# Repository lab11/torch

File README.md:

Torch
=====

<center>

</center>

This system provides the hardware and software for a software-defined lighting platform.

Compile
-------

    git clone https://github.com/lab11/contiki
    cd contiki
    git co sdl

    cd ../torch/contiki/apps/coap
    make

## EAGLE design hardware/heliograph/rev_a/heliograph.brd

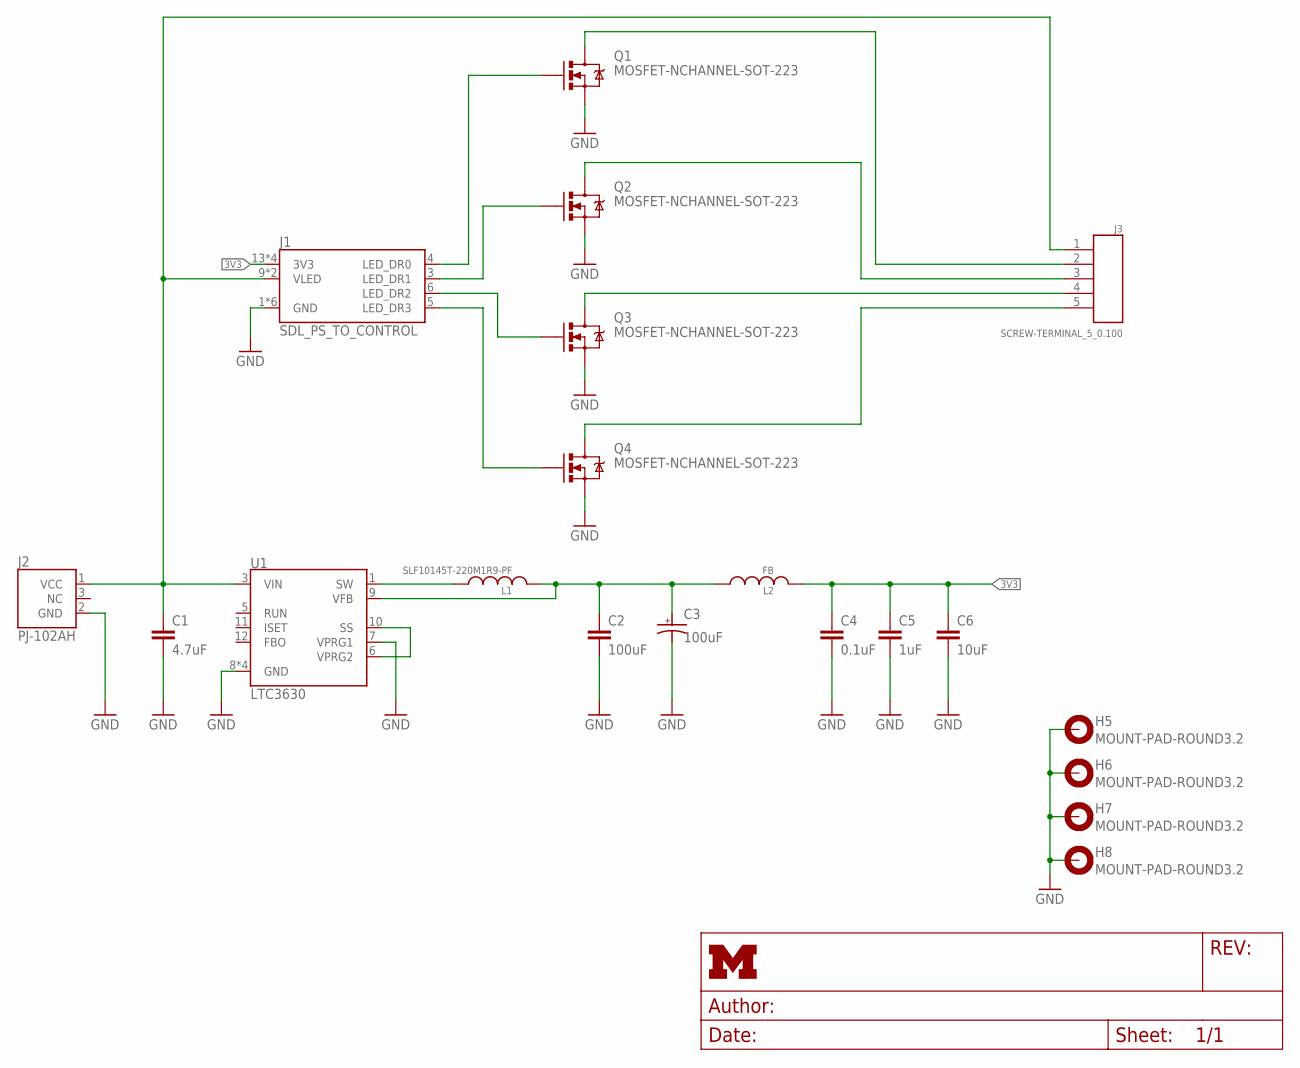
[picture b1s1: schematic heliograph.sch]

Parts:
C1: 4.7uF; C2220K; DIGIKEY 445-1450-1-ND
C2: 100uF; C1210; DIGIKEY 1276-3364-1-ND
C3: 100uF; 2917-POL; DIGIKEY 399-3769-1-ND
C4: 0.1uF; C0603; DIGIKEY 445-1316-1-ND
C5: 1uF; C0603; DIGIKEY 445-1604-1-ND
C6: 10uF; C0603; DIGIKEY 445-9065-1-ND
H5, H6, H7, H8: MOUNT-PAD-ROUND3.2; 3,2-PAD
J1: SDL_PS_TO_CONTROL
J2: PJ-102AH
J3: SCREW-TERMINAL_5_0.100; CONN_BLOCK_5
L1: SLF10145T-220M1R9-PF; SLF10145
L2: FB; 0603_CAP; DIGIKEY 490-1011-1-ND
Q1, Q2, Q3, Q4: MOSFET-NCHANNEL-SOT-223; SOT-223; DIGIKEY 568-9714-1-ND
U1: LTC3630; MSOP-16(12)

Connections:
3V3: C4.1, C5.1, C6.1, J1.13 (3V3), J1.14 (3V3), J1.15 (3V3), J1.16 (3V3), L2.2
GND: C1.2, C2.2, C3.- (ANODE), C4.2, C5.2, C6.2, H5.B3,2, H6.B3,2, H7.B3,2, H8.B3,2, J1.1 (GND), J1.2 (GND), J1.7 (GND), J1.8 (GND), J1.11 (GND), J1.12 (GND), J2.2 (GND), Q1.3 (S), Q2.3 (S), Q3.3 (S), Q4.3 (S), U1.7 (VPRG1), U1.8 (GND), U1.14 (GND), U1.16 (GND), U1.17 (GND)
unnamed: L1.1, U1.1 (SW)
unnamed: C2.1, C3.+ (CATHODE), L1.2, L2.1, U1.9 (VFB)
unnamed: U1.6 (VPRG2), U1.10 (SS)
unnamed: J1.4 (LED_DR0), Q1.1 (G)
unnamed: J1.3 (LED_DR1), Q2.1 (G)
unnamed: J1.6 (LED_DR2), Q3.1 (G)
unnamed: J1.5 (LED_DR3), Q4.1 (G)
unnamed: J3.3, Q2.2 (D), Q2.4 (D)
unnamed: J3.2, Q1.2 (D), Q1.4 (D)
unnamed: J3.5, Q4.2 (D), Q4.4 (D)
unnamed: J3.4, Q3.2 (D), Q3.4 (D)
VIN: C1.1, J1.9 (VLED), J1.10 (VLED), J2.1 (VCC), J3.1, U1.3 (VIN)

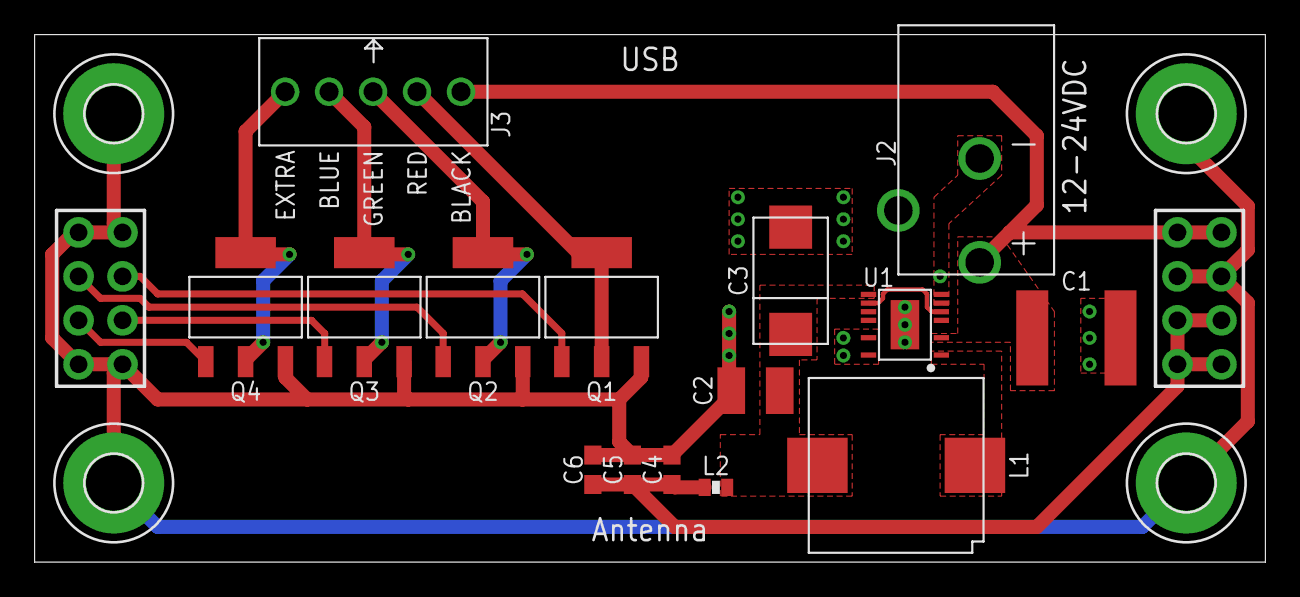
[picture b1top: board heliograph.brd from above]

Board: 2 copper layers, 71.1 x 30.5 mm, 20 parts (0 on the bottom side), 14 nets.

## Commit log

2014-09-26 Initial commit, add Torch project
2014-09-26 Add readme
2014-09-26 rename readme file
2015-01-27 SDL altium files
2015-03-02 add altium libraries for torch
2015-03-15 Altium files for 2nd version of led frontend
2015-03-17 added solidworks models
    start of frame, bulb holder
2015-03-17 version 3 of globe mount
2015-03-17 added frame assembly
2015-03-19 update contiki to new contiki
2015-03-19 add code for rfswitch
2015-03-20 control plane for sdl
2015-03-20 working on pwm
2015-03-20 pwm test
2015-03-21 coap app for torch
2015-03-21 Active High DTR pin. Fixes bootloader problem
    Requires update to cc2538-bsl script in Contiki
2015-03-21 `make fix` updates cc2538 to active high dtr
2015-03-25 updates to torch app
2015-03-25 added flash chip code
2015-03-25 add script for jlink
    doesn't work with cjtag
2015-03-25 quick python script for coap
2015-03-28 active low bootloader
2015-03-28 light conf script
2015-03-28 Add script to dump status
2015-03-28 Actually do 3 tries
2015-03-29 First pass at phone holder
    Add a holder for the lumia 1020 to mount on the OptiTrack calibration
    tool.
2015-03-30 Gen 2 phone holder
    A little more tolerance in phone holder; top thumb hole; clip corner
2015-03-30 Laser Range Holder for Calibration
    First pass
2015-04-04 Revise second hole size for OptiTrack
    Also increase tolerance on phone holder and thickness (stiffness) of
    phone holder.
2015-04-04 Tighten phone tol, loosen small hole tolerance
2015-04-05 Light conf from atrium deployment
2015-04-05 Save atrium conf elsewhere
2015-04-05 getting ready to do some mass programming
2015-04-05 dup script
2015-04-05 added extra sdl control boards
2015-04-07 Final Versions of Calibration Prints
    Thicker bases with holes. Fixes two screw sizes in OptiTrack holder.
2015-04-12 frame parts
2015-04-12 updated gitignore
2015-04-25 added torch mount
2015-04-25 updated app
2015-04-27 updates to app
2015-04-27 add heliograph board
    for RGB panels
2015-04-27 add outline of flare
2015-04-28 wall mount for globe
2015-06-01 Lights can correctly stay off on reboot
2015-06-13 added support for nRF51822 on torch
2015-06-13 updated squall
2015-06-14 bidirectional comm between ble and cc2538
2015-06-14 add gitignore
2015-06-14 start of script to pulse lights
2015-06-14 app that puts cc2538 in sleep and antenna -> ble
2015-10-27 update nrf code to new apis
2015-10-27 update to newer versions of contiki
2015-10-27 most basic updates to readme
2015-10-28 updated torch to compile and run again
2015-10-28 fix *100 bug
2015-10-28 updated nrf app to support main led control
2015-10-28 add images
2015-10-28 update to eddystone
2015-10-28 unix line endings
2015-10-28 add summon app
2015-10-28 add favicon
2015-10-28 actually use favicon
2015-10-28 add picture to readme
2016-01-14 Updated to use new nrf5x-base service API
